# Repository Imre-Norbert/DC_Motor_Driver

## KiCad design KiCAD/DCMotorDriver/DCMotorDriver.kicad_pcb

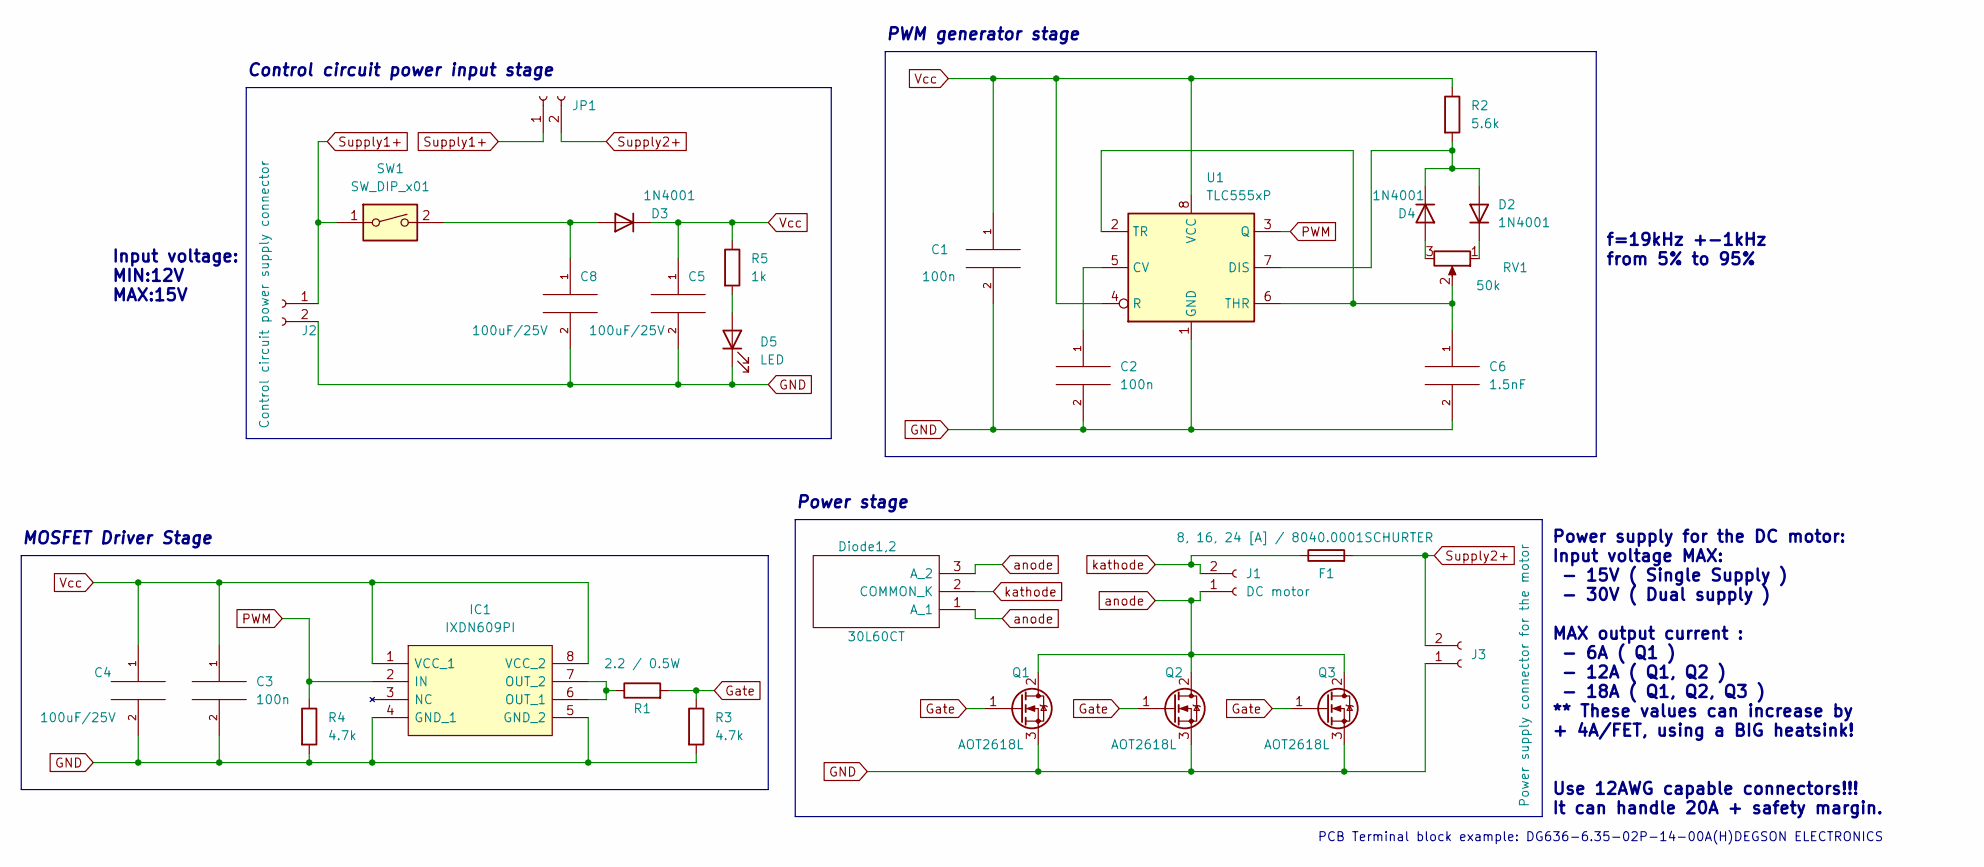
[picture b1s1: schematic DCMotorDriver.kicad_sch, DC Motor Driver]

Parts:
C1, C2, C3: 100n; C_Rect_L7.2mm_W2.5mm_P5.00mm_FKS2_FKP2_MKS2_MKP2
C4: 100uF/25V; C_Radial_D8.0mm_H11.5mm_P3.50mm
C5: 100uF/25V; C_Radial_D6.3mm_H11.0mm_P2.50mm
C6: 1.5nF; C_Rect_L7.2mm_W2.5mm_P5.00mm_FKS2_FKP2_MKS2_MKP2
C8: 100uF/25V; C_Radial_D12.5mm_H20.0mm_P5.00mm
D2, D3, D4: 1N4001; D_DO-41_SOD81_P10.16mm_Horizontal
D5: LED; LED_D5.0mm
Diode1,2: 30L60CT; TO-220-3_Vertical; Manufacturer_Part_Number MBRF10200CT; Mouser Part Number 576-MBRF10200CT
F1: 8, 16, 24 [A] / 8040.0001SCHURTER; Fuseholder_Clip-6.3x32mm_Littelfuse_102_122_Inline_P34.21x7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
IC1: IXDN609PI; DIP-8_W7.62mm; Manufacturer_Part_Number IXDN609PI; Mouser Part Number 849-IXDN609PI
J1: DC motor; JST_NV_B02P-NV_1x02_P5.00mm_Vertical
J2: Control circuit power supply connector; JST_NV_B02P-NV_1x02_P5.00mm_Vertical
J3: Power supply connector for the motor; JST_NV_B02P-NV_1x02_P5.00mm_Vertical
JP1: .; JST_NV_B02P-NV_1x02_P5.00mm_Vertical
Q1, Q2, Q3: AOT2618L; TO-220-3_Vertical
R1: 2.2 / 0.5W; R_Axial_DIN0207_L6.3mm_D2.5mm_P10.16mm_Horizontal
R2: 5.6k; R_Axial_DIN0204_L3.6mm_D1.6mm_P7.62mm_Horizontal
R3, R4: 4.7k; R_Axial_DIN0204_L3.6mm_D1.6mm_P7.62mm_Horizontal
R5: 1k; R_Axial_DIN0204_L3.6mm_D1.6mm_P7.62mm_Horizontal
RV1: 50k; Potentiometer_Piher_T-16H_Single_Horizontal
SW1: SW_DIP_x01; JST_NV_B02P-NV_1x02_P5.00mm_Vertical
U1: TLC555xP; DIP-8_W7.62mm

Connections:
GND: C1.2, C2.2, C3.2, C4.2, C5.2, C6.2, C8.2, D5.1 (K), IC1.4 (GND_1), IC1.5 (GND_2), J2.2, J3.1, Q1.3 (S), Q2.3 (S), Q3.3 (S), R3.2, R4.2, U1.1 (GND)
Gate: Q1.1 (G), Q2.1 (G), Q3.1 (G), R1.2, R3.1
unnamed: C2.1, U1.5 (CV)
unnamed: C6.1, RV1.2, U1.2 (TR), U1.6 (THR)
unnamed: C8.1, D3.2 (A), SW1.2
unnamed: D5.2 (A), R5.2
unnamed: IC1.6 (OUT_1), IC1.7 (OUT_2), R1.1
unnamed: D2.2 (A), D4.1 (K), R2.2, U1.7 (DIS)
unnamed: D2.1 (K), RV1.1
unnamed: D4.2 (A), RV1.3
PWM: IC1.2 (IN), R4.1, U1.3 (Q)
Supply1+: J2.1, JP1.1, SW1.1
Supply2+: F1.2, J3.2, JP1.2
Vcc: C1.1, C3.1, C4.1, C5.1, D3.1 (K), IC1.1 (VCC_1), IC1.8 (VCC_2), R2.1, R5.1, U1.4 (R), U1.8 (VCC)
anode: Diode1,2.1 (A_1), Diode1,2.3 (A_2), J1.1 (Pin_2), Q1.2 (D), Q2.2 (D), Q3.2 (D)
kathode: Diode1,2.2 (COMMON_K), F1.1, J1.2 (Pin_1)

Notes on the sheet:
Input voltage: MIN:12V MAX:15V
PWM generator stage
Control circuit power input stage
Power supply for the DC motor: Input voltage MAX: - 15V ( Single Supply ) - 30V ( Dual supply ) MAX output current : - 6A ( Q1 ) - 12A ( Q1, Q2 ) - 18A ( Q1, Q2, Q3 ) ** These values can increase by + 4A/FET, using a BIG heatsink! Use 12AWG capable connectors!!! It can handle 20A + safety margin.
MOSFET Driver Stage
f=19kHz +-1kHz from 5% to 95%
Power stage
PCB Terminal block example: DG636-6.35-02P-14-00A(H)DEGSON ELECTRONICS

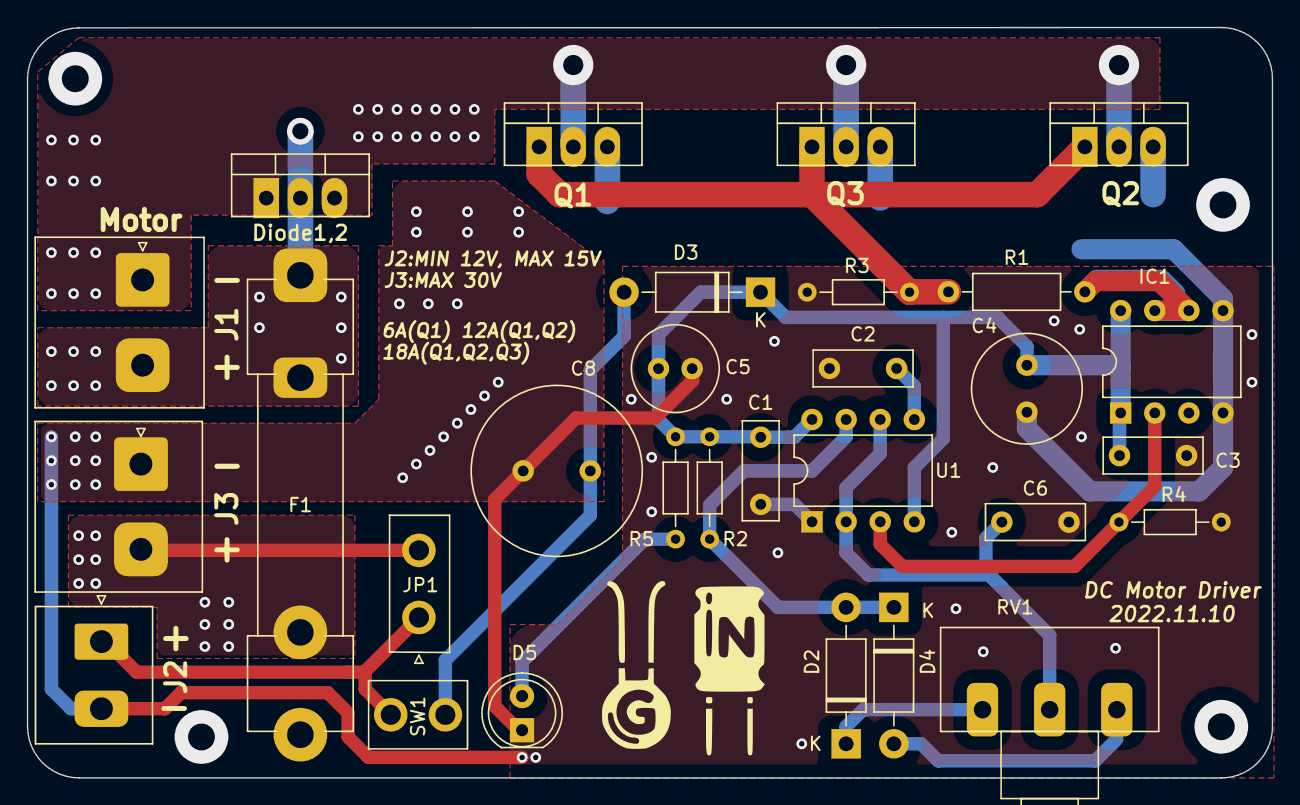
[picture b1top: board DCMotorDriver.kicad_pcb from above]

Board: 2 copper layers, 92.7 x 55.9 mm, 29 parts (0 on the bottom side), 16 nets.

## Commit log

2022-12-04 The project is completed, remaining tasks include: Writing user manual, uploading some pictures and maybe test measurements of the final pcb.
